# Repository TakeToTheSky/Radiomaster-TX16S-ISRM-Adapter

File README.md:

# Radiomaster-TX16S-ISRM-Adapter
Radiomaster TX16S ISRM Adapter

This project was created to allow the Radiomaster TX16S radio transmitter to run the Frsky Access RF protocol.  The ISRM module used is the module available to upgrade the Frsky Horus X10S radio to the Access RF protocol.  I have designed a PCB with the same footprint as the Radiomaster TX16S 4 in 1 multimodule RF board.  This allows the adapter to attach to the existing mounting brackets.

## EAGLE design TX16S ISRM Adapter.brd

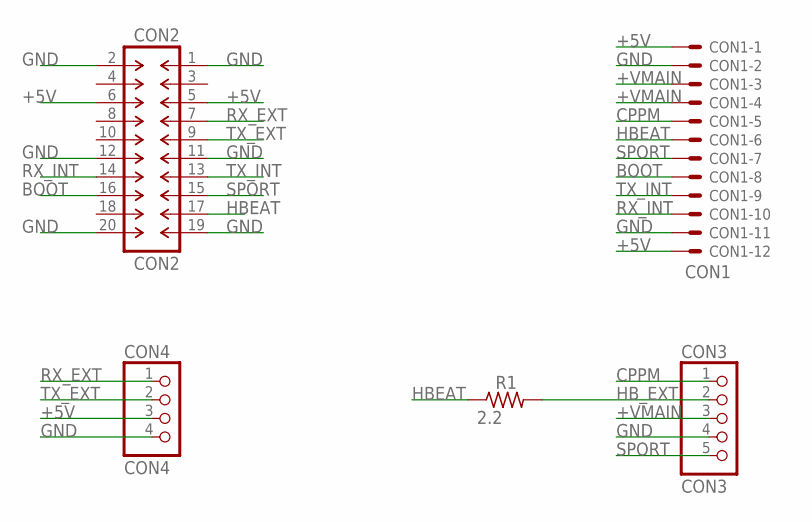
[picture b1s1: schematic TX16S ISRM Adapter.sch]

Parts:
CON1: CON1; 53048-12
CON2: CON2; DIL-2MM-2X10_M
CON3: CON3; 1X05
CON4: CON4; 1X04
R1: 2.2; R0603

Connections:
+5V: CON1.1, CON1.12, CON2.5, CON2.6, CON4.3
+VMAIN: CON1.3, CON1.4, CON3.3
BOOT: CON1.8, CON2.16
CPPM: CON1.5, CON3.1
GND: CON1.2, CON1.11, CON2.1, CON2.2, CON2.11, CON2.12, CON2.19, CON2.20, CON3.4, CON4.4 (GND)
HBEAT: CON1.6, CON2.17, R1.1
HB_EXT: CON3.2, R1.2
RX_EXT: CON2.7, CON4.1
RX_INT: CON1.10, CON2.14
SPORT: CON1.7, CON2.15, CON3.5
TX_EXT: CON2.9, CON4.2
TX_INT: CON1.9, CON2.13

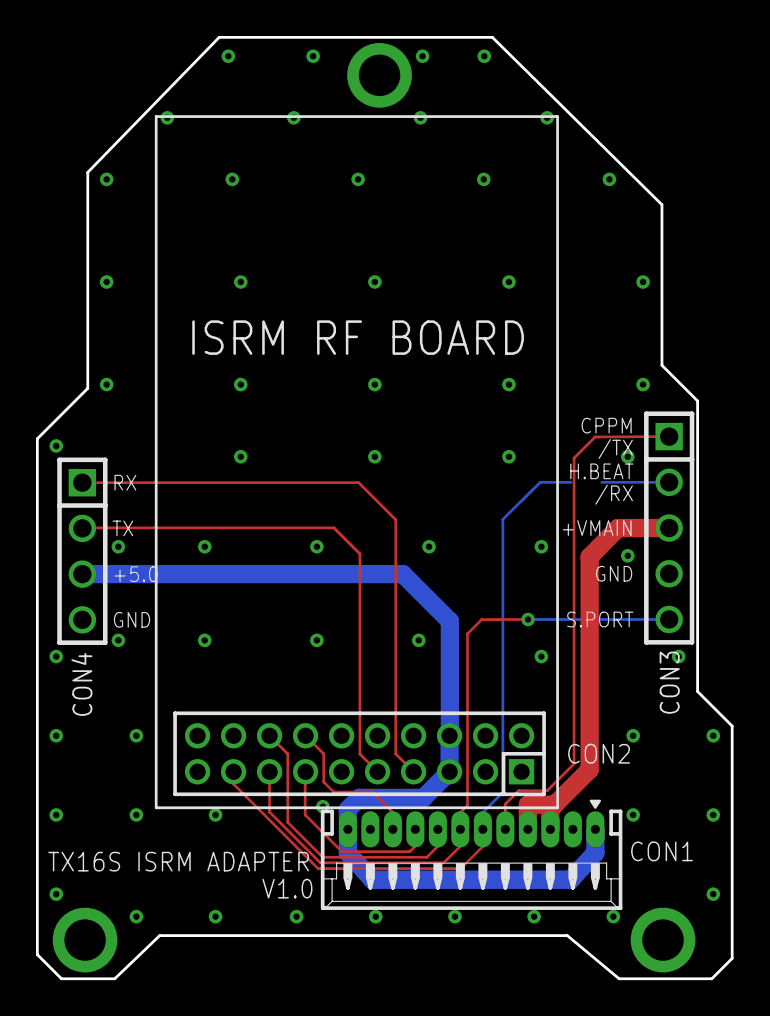
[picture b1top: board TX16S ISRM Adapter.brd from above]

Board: 2 copper layers, 38.6 x 52.3 mm, 8 parts (1 on the bottom side), 12 nets.

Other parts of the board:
E$1, E$2, E$3: 2,3-PAD

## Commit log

2022-07-18 Create Eagle PCB Files
2022-07-18 Rename TX16S ISRM Adapter.brd to Eagle PCB Files/TX16S ISRM Adapter.brd
2022-07-18 Rename TX16S ISRM Adapter.sch to Eagle PCB Files/TX16S ISRM Adapter.sch

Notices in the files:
parts and their libraries:
con-headers-jp-DK: Copyright (C) 2008, Bob Starr
